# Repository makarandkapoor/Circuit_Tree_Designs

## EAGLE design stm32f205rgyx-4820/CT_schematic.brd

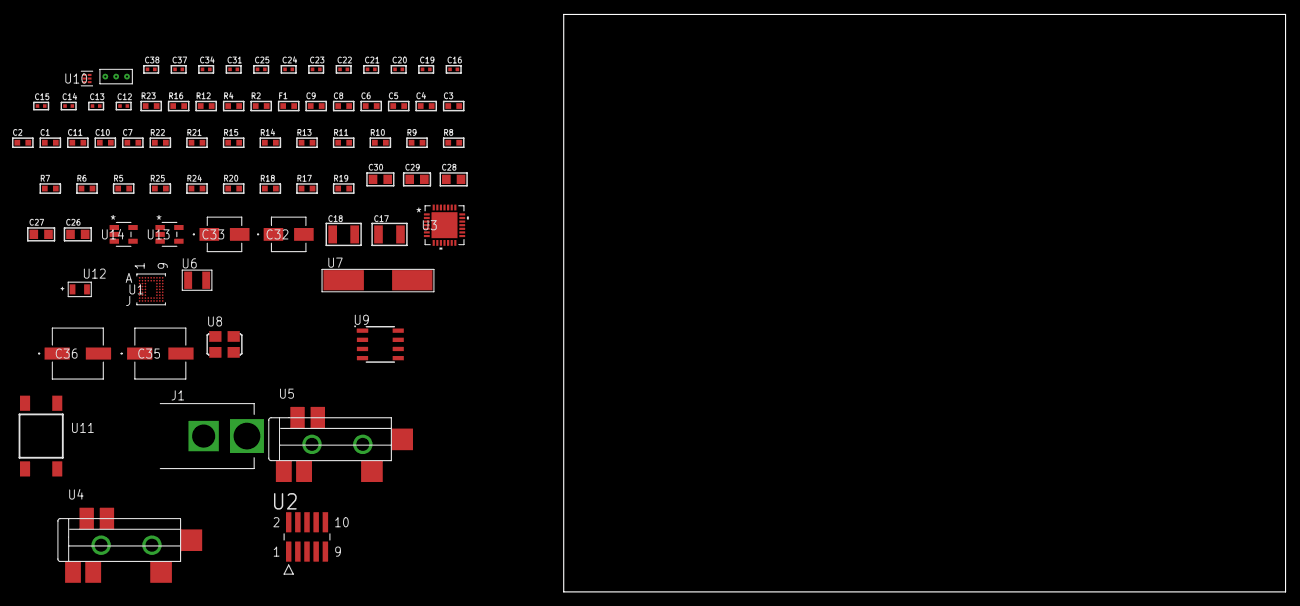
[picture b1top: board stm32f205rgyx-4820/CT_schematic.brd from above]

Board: 2 copper layers, 100.0 x 80.0 mm, 78 parts (0 on the bottom side), 38 nets, no tracks yet.

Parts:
C1, C9: 1e-06; C0603
C2, C3, C4, C5, C6: 1e-07; C0603
C7: 4.7e-06; C0603
C8: 1e-08; C0603
C10, C11: 2.2e-06; C0603
C12, C13, C14, C15: 1e-11; C0402
C16, C21, C22, C23, C24, C25, C34: 1e-07; C0402
C17, C18: 2.2e-05; C1210
C19, C20: 1e-09; C0402
C26, C27, C28, C29, C30: 1e-05; C0805
C31, C37, C38: 1e-08; C0402
C32: 1e-06; EXV-9B
C33: 2.2e-06; EXV-9B
C35, C36: 0.0001; EXV-9H
F1: 240.0; L0603
J1: PJ-037B; PJ-037B_PACKAGE
R2: 1000.0; R0603
R4: 4700.0; R0603
R5, R6, R7, R8, R9, R10, R11, R21, R22: 10000.0; R0603
R12: 5.0; R0603
R13, R14, R15: 47000.0; R0603
R16: 680.0; R0603
R17, R18, R20: 100000.0; R0603
R19: 164658.62; R0603
R23: 9100.0; R0603
R24: 680000.0; R0603
R25: 120000.0; R0603
U1: STM32F205RGY6; WLCSP66
U2: FTSH-105-01-L-DV-K; SAMTEC_FTSH-105-01-L-DV-K
U3: WM8731CLSEFL; QFN-28
U4, U5: SJ-43515TS-SMT-TR
U6: ABS07-32.768KHZ-7-T
U7: ABLS-25.000MHZ-B2F-T
U8: ASFL1-12.288MHZ-EC-T; ASFL1
U9: LP2954AIMX/NOPB; LP2954
U10: TPS3895ADRYR; SON-6
U11: 4-1437565-2; SW_4-1437565-2
U12: Q65110A2395; LGM67K-G1J2-24-Z
U13, U14: nc7sz125m5x; NC7SZ125M5X
U15: Dummy; DUMMY_PACKAGE_157

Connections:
CLK_CRYSTAL_U1_B9: C12.1, U1.B9, U6.1
CLK_CRYSTAL_U1_C9: C13.1, U1.C9, U6.2
CLK_CRYSTAL_U1_E9: C14.1, U1.E9, U7.1
CLK_CRYSTAL_U1_F9: C15.1, U1.F9, U7.2
CLK_U3_1: U3.1, U8.3
GND: C1.2, C2.2, C3.2, C4.2, C5.2, C6.2, C7.2, C8.2, C9.2, C10.2, C11.2, C12.2, C13.2, C14.2, C15.2, C16.2, C20.2, C21.2, C22.2, C23.2, C24.2, C25.2, C26.2, C27.2, C28.2, C29.2, C30.2, C31.2, C32.2, C33.2, C34.2, C35.2, C36.2, C37.2, C38.2, J1.2, R2.2, R5.2, R6.2, R7.2, R11.2, R12.2, R13.2, R14.2, R15.2, R20.2, R23.2, R25.2, U1.B1, U1.D8, U1.F1, U1.H9, U2.3, U2.5, U3.4, U3.15, U3.19, U3.25, U3.26, U3.29, U4.1, U5.1, U8.2, U9.4, U10.2, U12.C, U13.2, U13.3, U14.1, U14.3, U15.1
NET_U1_B6: R5.1, U1.B6
NET_U1_C2: C11.1, U1.C2
NET_U1_C8: R7.1, U1.C8
NET_U1_E8: R4.1, U1.E8, U14.4
NET_U1_F7: C8.1, C9.1, F1.1, U1.F7
NET_U1_H7: R6.1, U1.H7
NET_U1_J3: C10.1, U1.J3
NET_U1_J9: U11.3, U11.4
NET_U2_9: R12.1, U2.9
NET_U3_20: C25.1, C30.1, U3.20
NET_U4_2: C18.1, R14.1, U4.2
NET_U4_5: C17.1, R13.1, U4.5
NET_U5_5: C19.1, C20.1, R15.1, R16.1, U5.5
NET_U9_3: R18.1, U9.3
NET_U9_5: R17.1, U9.5
NET_U9_7: R19.2, R20.1, U9.7
NET_U10_1: R22.1, R23.1, U10.1
NET_U10_3: R24.2, R25.1, U10.3
NET_U10_4: R21.1, U10.4, U13.4, U14.2
NET_U11_1: R2.1, U11.1, U11.2
PROC_ADC1_IN1: U1.H8, U15.2
PROC_ADC1_IN3: U1.G7, U15.3
PROC_I2S2_SCK: U1.H2, U3.7
PROC_I2S2_SD: U1.G1, U3.8
PROC_I2S2_WS: U1.A7, U3.9, U3.11
PROC_SYS_JTCK_SWCLK: R11.1, U1.A1, U2.4
PROC_SYS_JTDI: R9.1, U1.A2, U2.8
PROC_SYS_JTDO_SWO: U1.A4, U2.6
PROC_SYS_JTMS_SWDIO: R10.1, U1.B2, U2.2
RST_OUT_U2_JTAG_RST_B: R8.1, U2.10, U13.1
VCC_S1_7V0: C32.1, C35.1, C36.1, J1.1, R18.2, U9.8
VCC_TIER1_3V3: C1.1, C2.1, C3.1, C4.1, C5.1, C6.1, C7.1, C16.1, C21.1, C22.1, C23.1, C24.1, C26.1, C27.1, C28.1, C29.1, C31.1, C33.1, C34.1, C37.1, C38.1, F1.2, R4.2, R8.2, R9.2, R10.2, R17.2, R19.1, R21.2, R22.2, R24.1, U1.A8, U1.A9, U1.D9, U1.E1, U2.1, U3.3, U3.5, U3.12, U3.18, U8.4, U9.1, U10.6, U13.5, U14.5

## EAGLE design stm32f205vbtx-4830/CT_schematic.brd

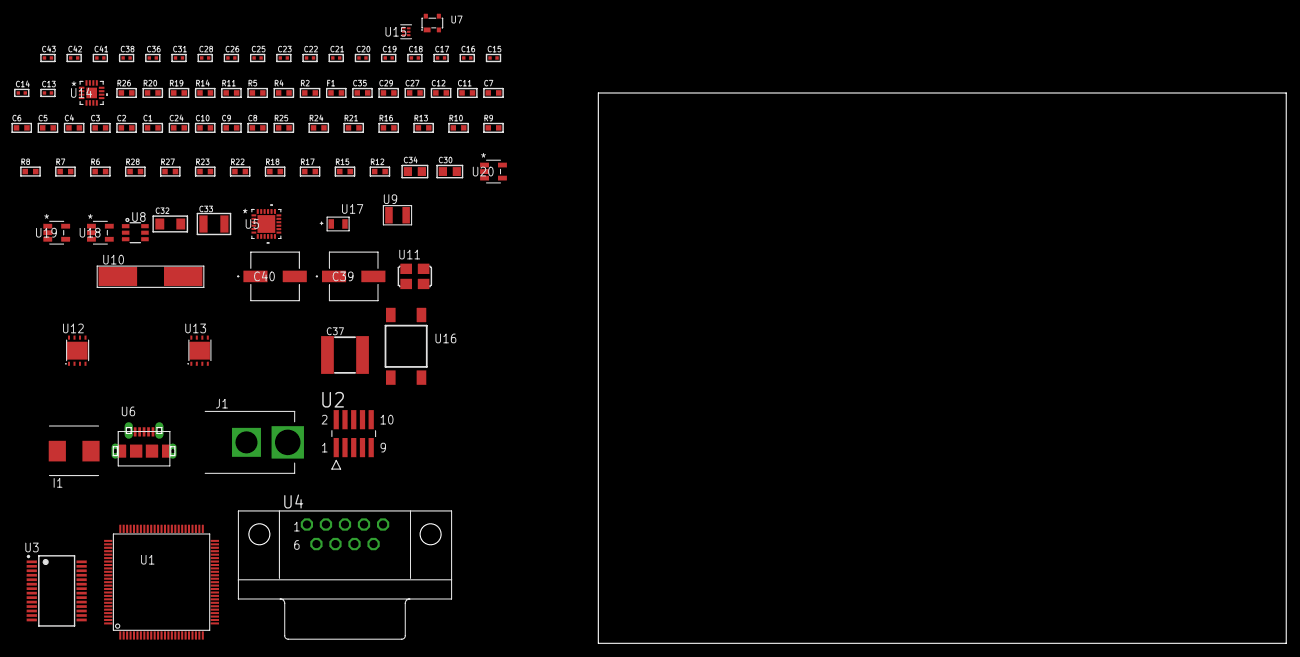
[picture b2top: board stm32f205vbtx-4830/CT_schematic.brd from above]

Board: 2 copper layers, 92 parts (0 on the bottom side), 71 nets, no tracks yet.

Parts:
C1, C12, C27, C29, C35: 1e-06; C0603
C2, C3, C4, C5, C6, C7: 1e-07; C0603
C8: 4.7e-06; C0603
C9, C10, C24: 2.2e-06; C0603
C11: 1e-08; C0603
C13, C14, C15, C16: 1e-11; C0402
C17, C18, C19, C20, C21, C22, C36, C38: 1e-07; C0402
C23, C25, C26, C28, C31, C41, C42, C43: 1e-08; C0402
C30, C34: 1e-05; C0805
C32: 1e-05; C1206
C33: 1e-05; C1210
C37: 6.8e-05; 2220
C39, C40: 0.0001; EXV-9H
F1: 240.0; L0603
I1: 3.3e-06; WE-HCI_7030/7040/7050
J1: PJ-037B; PJ-037B_PACKAGE
R2, R20: 1000.0; R0603
R4, R5: 4700.0; R0603
R6, R7, R8, R9, R10, R24, R25: 10000.0; R0603
R11: 5.0; R0603
R12, R15, R17, R18: 100000.0; R0603
R13: 47000.0; R0603
R14: 8060.0; R0603
R16: 36000.0; R0603
R19: 2231.0; R0603
R21: 20000.0; R0603
R22: 150000.0; R0603
R23: 300000.0; R0603
R26: 9100.0; R0603
R27: 680000.0; R0603
R28: 120000.0; R0603
U1: STM32F205VBT6; LQFP100
U2: FTSH-105-01-L-DV-K; SAMTEC_FTSH-105-01-L-DV-K
U3: ST3241EBPR; SSOP-28
U4: 182-009-113R531; 182-009-MALE
U5: USB3317C-CP-TR; QFN-24
U6: 47590-0001; MICRO_USB_AB
U7: prtr5v0u2ax; SOT143B
U8: MAX4995AAUT+T; SOT-23-6
U9: ABS07-32.768KHZ-7-T
U10: ABLS-25.000MHZ-B2F-T
U11: ASFL1-26MHZ-NCS; ASFL1
U12: LP2951ACSDX/NOPB; WSON-8
U13: LP3878SDX-ADJ/NOPB; WSON-8
U14: LTC3601EUD#PBF; QFN-16_EP
U15: TPS3895ADRYR; SON-6
U16: 4-1437565-2; SW_4-1437565-2
U17: Q65110A2395; LGM67K-G1J2-24-Z
U18, U19, U20: nc7sz125m5x; NC7SZ125M5X

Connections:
CLK_CRYSTAL_U1_8: C13.1, U1.8, U9.1
CLK_CRYSTAL_U1_9: C14.1, U1.9, U9.2
CLK_CRYSTAL_U1_12: C15.1, U1.12, U10.1
CLK_CRYSTAL_U1_13: C16.1, U1.13, U10.2
CLK_U5_23: U5.23, U11.3
GND: C1.2, C2.2, C3.2, C4.2, C5.2, C6.2, C7.2, C8.2, C9.2, C10.2, C11.2, C12.2, C13.2, C14.2, C15.2, C16.2, C17.2, C18.2, C21.2, C22.2, C23.2, C24.2, C25.2, C26.2, C27.2, C28.2, C29.2, C30.2, C31.2, C32.2, C33.2, C34.2, C35.2, C37.1, C37.2, C38.2, C39.2, C40.2, C41.2, C42.2, C43.2, J1.2, R2.2, R6.2, R10.2, R11.2, R13.2, R14.2, R17.2, R20.2, R21.2, R23.2, R26.2, R28.2, U1.10, U1.20, U1.27, U1.74, U2.3, U2.5, U3.23, U3.25, U4.5, U5.25, U6.5, U6.6, U6.7, U6.8, U6.9, U7.1, U8.2, U11.2, U12.3, U12.4, U12.PAD, U13.3, U13.PAD, U14.1, U14.9, U14.17, U15.2, U17.C, U18.2, U18.3, U19.1, U19.3, U20.1, U20.3
NET_U1_14: R4.1, U1.14, U19.4
NET_U1_22: C11.1, C12.1, F1.1, U1.21, U1.22
NET_U1_49: C9.1, U1.49
NET_U1_73: C10.1, U1.73
NET_U1_94: R6.1, U1.94
NET_U1_98: U16.3, U16.4
NET_U2_9: R11.1, U2.9
NET_U3_1: C20.1, U3.1
NET_U3_2: C20.2, U3.2
NET_U3_3: C22.1, U3.3
NET_U3_22: R12.1, U3.22
NET_U3_24: C19.2, U3.24
NET_U3_27: C21.1, U3.27
NET_U3_28: C19.1, U3.28
NET_U4_2: U3.4, U4.2
NET_U4_3: U3.9, U4.3
NET_U4_7: U3.5, U4.7
NET_U4_8: U3.10, U4.8
NET_U5_4: C24.1, U5.4
NET_U5_22: R5.1, U5.22, U20.4
NET_U5_24: R14.1, U5.24
NET_U6_1: C27.1, U5.2, U6.1, U7.4, U8.1
NET_U6_2: U5.5, U6.2, U7.3
NET_U6_3: U5.6, U6.3, U7.2
NET_U6_4: U5.1, U6.4
NET_U8_3: R13.1, U8.3
NET_U8_4: U5.7, U8.4
NET_U12_5: R15.1, U12.5
NET_U12_7: R16.2, R17.1, U12.7
NET_U13_1: C31.1, U13.1
NET_U13_6: R19.2, R20.1, U13.6
NET_U13_8: R18.1, U13.8
NET_U14_3: C36.2, I1.1, U14.3, U14.4
NET_U14_6: C36.1, U14.6
NET_U14_7: C35.1, U14.7, U14.12
NET_U14_10: R23.1, U14.10
NET_U14_11: R21.1, R22.1, U14.11
NET_U14_ATNET_3: I1.2, R22.2
NET_U15_1: R25.1, R26.1, U15.1
NET_U15_3: R27.2, R28.1, U15.3
NET_U15_4: R24.1, U15.4, U18.4, U19.2, U20.2
NET_U16_1: R2.1, U16.1, U16.2
PROC_SYS_JTCK_SWCLK: R10.1, U1.76, U2.4
PROC_SYS_JTDI: R8.1, U1.77, U2.8
PROC_SYS_JTDO_SWO: U1.89, U2.6
PROC_SYS_JTMS_SWDIO: R9.1, U1.72, U2.2
PROC_UART4_RX: U1.24, U3.19
PROC_UART4_TX: U1.23, U3.14
PROC_USB_OTG_HS_ULPI_CK: U1.30, U5.12
PROC_USB_OTG_HS_ULPI_D0: U1.26, U5.16
PROC_USB_OTG_HS_ULPI_D1: U1.35, U5.15
PROC_USB_OTG_HS_ULPI_D2: U1.36, U5.14
PROC_USB_OTG_HS_ULPI_D3: U1.47, U5.13
PROC_USB_OTG_HS_ULPI_D4: U1.48, U5.11
PROC_USB_OTG_HS_ULPI_D5: U1.51, U5.10
PROC_USB_OTG_HS_ULPI_D6: U1.52, U5.9
PROC_USB_OTG_HS_ULPI_D7: U1.91, U5.8
PROC_USB_OTG_HS_ULPI_DIR: U1.17, U5.19
PROC_USB_OTG_HS_ULPI_NXT: U1.18, U5.18
PROC_USB_OTG_HS_ULPI_STP: U1.15, U5.20
RST_OUT_U2_JTAG_RST_B: R7.1, U2.10, U18.1
VCC_S1_5V9: C29.1, C32.1, C34.1, C39.1, C40.1, J1.1, R18.2, U12.8, U13.4, U14.15, U14.16
VCC_TIER1_1V8: C26.1, C30.1, C41.1, C42.1, C43.1, R15.2, R16.1, U5.21, U12.1, U18.5, U19.5, U20.5
VCC_TIER1_3V3: C1.1, C2.1, C3.1, C4.1, C5.1, C6.1, C7.1, C8.1, C17.1, C18.1, C23.1, C25.1, C28.1, C33.1, C38.1, F1.2, R4.2, R5.2, R7.2, R8.2, R9.2, R12.2, R19.1, R24.2, R25.2, R27.1, U1.6, U1.11, U1.19, U1.28, U1.50, U1.75, U1.100, U2.1, U3.26, U5.3, U5.17, U11.4, U13.5, U15.6
VCC_TIER1_5V0: C37.2, I1.2, R22.2, U8.5, U14.8

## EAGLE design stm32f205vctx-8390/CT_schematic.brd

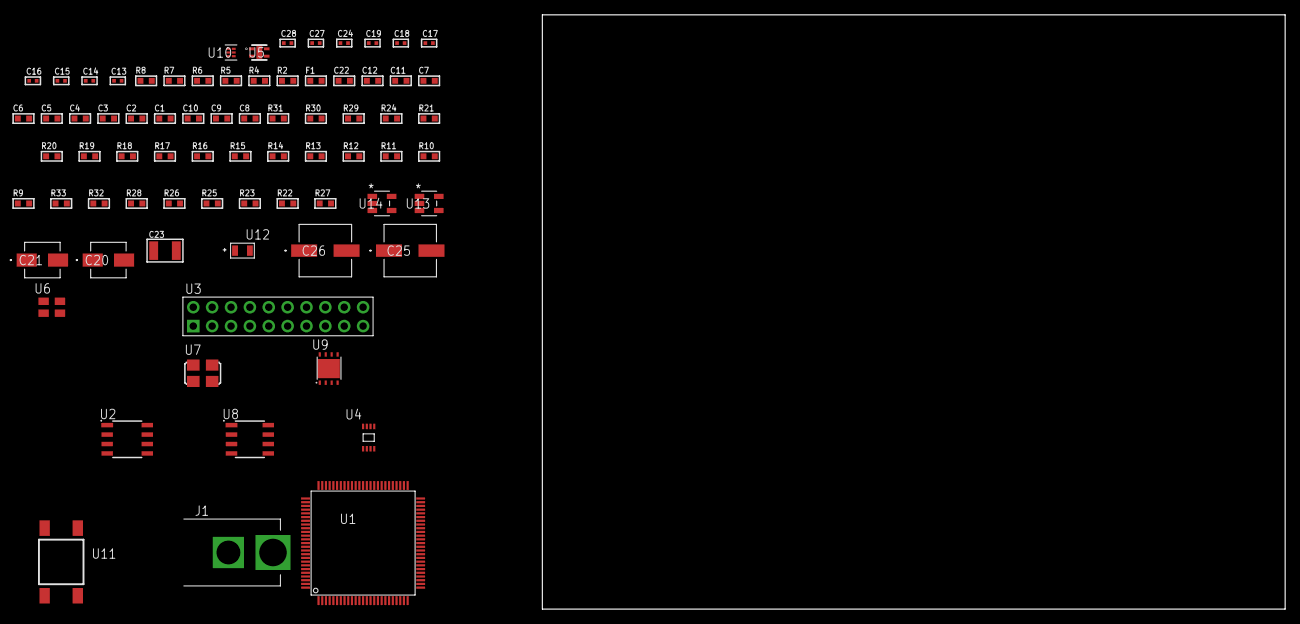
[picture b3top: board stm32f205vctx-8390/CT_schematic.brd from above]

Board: 2 copper layers, 100.0 x 80.0 mm, 75 parts (0 on the bottom side), 41 nets, no tracks yet.

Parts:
C1, C12: 1e-06; C0603
C2, C3, C4, C5, C6, C7: 1e-07; C0603
C8: 4.7e-06; C0603
C9, C10: 2.2e-06; C0603
C11: 1e-08; C0603
C13, C16, C18, C19, C27, C28: 1e-08; C0402
C14, C15, C17, C24: 1e-07; C0402
C20: 1e-06; EXV-9B
C21: 2.2e-06; EXV-9B
C22: 8e-07; R0603
C23: 1e-05; C1210
C25, C26: 0.0001; EXV-9H
F1: 240.0; L0603
J1: PJ-037B; PJ-037B_PACKAGE
R2: 1000.0; R0603
R4: 4700.0; R0603
R5, R6, R7, R8: 2200.0; R0603
R9, R10, R11, R12, R13, R14, R15, R16, R17, R18, R19, R20, R21, R29, R30: 10000.0; R0603
R22, R23, R25, R26, R28: 100000.0; R0603
R24: 47000.0; R0603
R27: 153694.38; R0603
R31: 82000.0; R0603
R32: 300000.0; R0603
R33: 120000.0; R0603
U1: STM32F205VCT6; LQFP100
U2: AT25040B-SSHL-T; SOIC-8
U3: TST-110-05-T-D-RA
U4: 24AA64T-I/MNY; TDFN-8/6MM
U5: Si7034-A10-IM; SI7034-A10-IM
U6: ASEK-32.768KHz-ECST; ASEK
U7: ASFL1-25MHZ-NCS; ASFL1
U8: LP2954AIMX/NOPB; LP2954
U9: LP2951ACSDX/NOPB; WSON-8
U10: TPS3895ADRYR; SON-6
U11: 4-1437565-2; SW_4-1437565-2
U12: Q65110A2395; LGM67K-G1J2-24-Z
U13, U14: nc7sz125m5x; NC7SZ125M5X

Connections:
CLK_U1_8: U1.8, U6.3
CLK_U1_12: U1.12, U7.3
GND: C1.2, C2.2, C3.2, C4.2, C5.2, C6.2, C7.2, C8.2, C9.2, C10.2, C11.2, C12.2, C13.2, C14.2, C15.2, C16.2, C17.2, C18.2, C19.2, C20.2, C21.2, C22.2, C23.2, C24.2, C25.2, C26.2, C27.2, C28.2, J1.2, R2.2, R9.2, R18.2, R20.2, R25.2, R28.2, R31.2, R33.2, U1.10, U1.27, U1.74, U2.4, U3.4, U3.6, U3.8, U3.10, U3.12, U3.14, U3.16, U3.18, U3.20, U4.4, U4.7, U5.5, U6.2, U7.2, U8.4, U9.3, U9.4, U9.PAD, U10.2, U12.C, U13.2, U13.3, U14.1, U14.3
NET_U1_14: R4.1, U1.14, U14.4
NET_U1_22: C11.1, C12.1, F1.1, U1.22
NET_U1_47: R7.1, U1.47, U4.6
NET_U1_48: R8.1, U1.48, U4.5
NET_U1_49: C9.1, U1.49
NET_U1_73: C10.1, U1.73
NET_U1_92: R5.1, U1.92, U5.2
NET_U1_93: R6.1, U1.93, U5.4
NET_U1_94: R9.1, U1.94
NET_U1_98: U11.3, U11.4
NET_U2_3: R10.1, U2.3
NET_U2_7: R12.1, U2.7
NET_U3_19: R18.1, U3.19
NET_U4_1: R19.1, U4.1
NET_U4_2: R20.1, U4.2
NET_U4_3: R21.1, U4.3
NET_U8_3: R23.1, U8.3
NET_U8_5: R22.1, U8.5
NET_U8_7: R24.2, R25.1, U8.7
NET_U9_5: R26.1, U9.5
NET_U9_7: R27.2, R28.1, U9.7
NET_U10_1: R30.1, R31.1, U10.1
NET_U10_3: R32.2, R33.1, U10.3
NET_U10_4: R29.1, U10.4, U13.4, U14.2
NET_U11_1: R2.1, U11.1, U11.2
PROC_SPI1_MISO: U1.31, U2.2
PROC_SPI1_MOSI: U1.32, U2.5
PROC_SPI1_NSS: R11.1, U1.29, U2.1
PROC_SPI1_SCK: U1.30, U2.6
PROC_SYS_JTCK_SWCLK: R16.1, U1.76, U3.9
PROC_SYS_JTDI: R14.1, U1.77, U3.5
PROC_SYS_JTDO_SWO: U1.89, U3.13
PROC_SYS_JTMS_SWDIO: R15.1, U1.72, U3.7
PROC_SYS_JTRST: R13.1, U1.90, U3.3
RST_OUT_U3_SRESET_B: R17.1, U3.15, U13.1
VCC_S1_14V8: C20.1, C22.1, C25.1, C26.1, J1.1, R23.2, U8.8, U9.8
VCC_TIER1_1V8: C1.1, C2.1, C3.1, C4.1, C5.1, C6.1, C7.1, C8.1, C13.1, C15.1, C16.1, C17.1, C21.1, C24.1, C27.1, C28.1, F1.2, R4.2, R5.2, R6.2, R7.2, R8.2, R10.2, R11.2, R12.2, R13.2, R14.2, R15.2, R16.2, R17.2, R19.2, R21.2, R22.2, R24.1, R29.2, R30.2, R32.1, U1.6, U1.11, U1.19, U1.28, U1.50, U1.75, U1.100, U2.8, U3.1, U4.8, U5.1, U8.1, U10.6, U13.5, U14.5
VCC_TIER1_3V3: C14.1, C18.1, C19.1, C23.1, R26.2, R27.1, U3.2, U6.4, U7.4, U9.1

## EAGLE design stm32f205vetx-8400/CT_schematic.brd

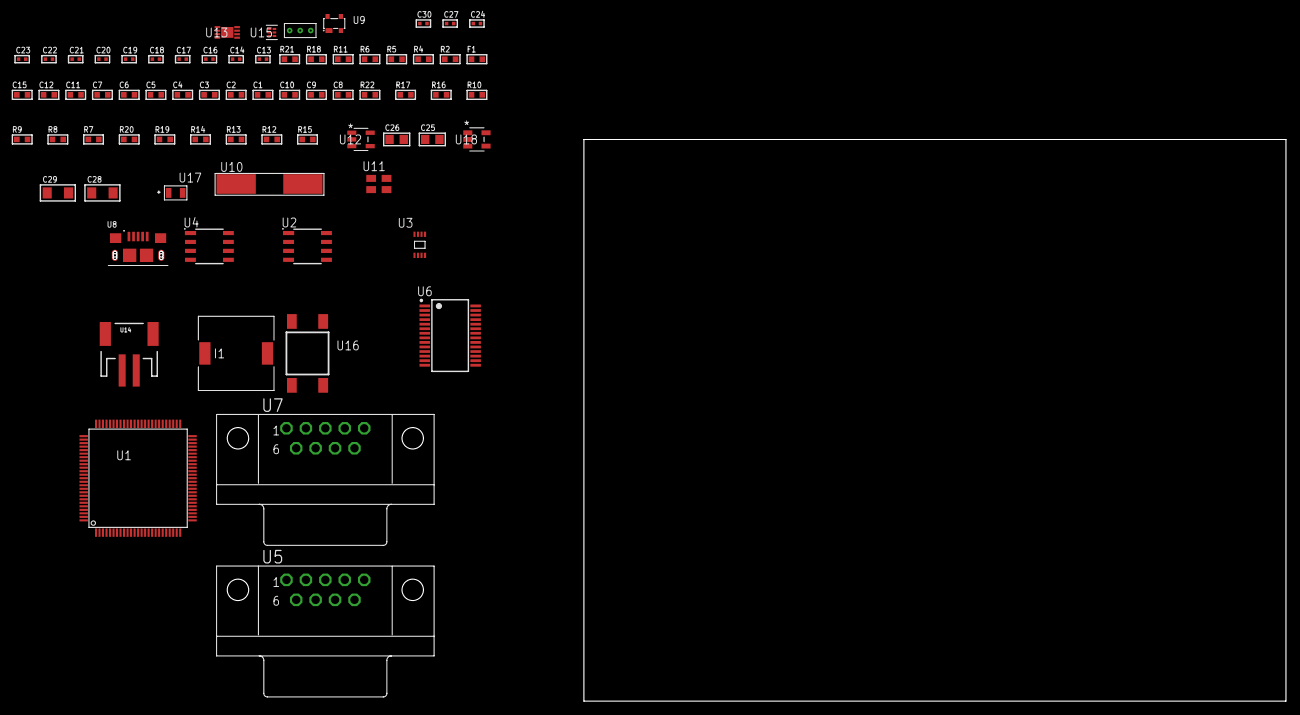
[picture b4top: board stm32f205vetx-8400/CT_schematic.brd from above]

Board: 2 copper layers, 71 parts (0 on the bottom side), 53 nets, no tracks yet.

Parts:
C1, C12, C15: 1e-06; C0603
C2, C3, C4, C5, C6, C7: 1e-07; C0603
C8: 4.7e-06; C0603
C9, C10: 2.2e-06; C0603
C11: 1e-08; C0603
C13, C14: 1e-11; C0402
C16, C17, C24, C30: 1e-08; C0402
C18, C19, C20, C21, C22, C23, C27: 1e-07; C0402
C25, C26: 1e-05; C0805
C28, C29: 1e-05; C1206
F1: 240.0; L0603
I1: 2.5e-06; DR1040
R2: 1000.0; R0603
R4: 4700.0; R0603
R5, R6: 2200.0; R0603
R7, R8, R9, R10, R16, R17, R22: 10000.0; R0603
R11: 120.0; R0603
R12: 470000.0; R0603
R13: 100000.0; R0603
R14: 220000.0; R0603
R15: 1000000.0; R0603
R18: 9100.0; R0603
R19: 680000.0; R0603
R20: 120000.0; R0603
R21: 2000.0; R0603
U1: STM32F205VET7; LQFP100
U2: AT25040B-SSHL-T; SOIC-8
U3: 24AA00T-I/MNY; TDFN-8/6MM
U4: SN65HVD230D; SOIC-8
U5, U7: 182-009-113R531; 182-009-MALE
U6: ST3241EBPR; SSOP-28
U8: 10118193-0001LF; FCI_10118193-0001LF
U9: prtr5v0u2ax; SOT143B
U10: ABLS-25.000MHZ-B2F-T
U11: ASEK-32.768KHz-ECST; ASEK
U12: ltc3406es5; TSOT-23-5
U13: MCP73831T-2ACI/MC; DFN8_2X3MC
U14: S2B-PH-SM4-TB(LF)(SN); JST-2-SMD
U15: TPS3895ADRYR; SON-6
U16: 4-1437565-2; SW_4-1437565-2
U17: Q65110A2395; LGM67K-G1J2-24-Z
U18: nc7sz125m5x; NC7SZ125M5X
U19: Dummy; DUMMY_PACKAGE_156

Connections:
CLK_CRYSTAL_U1_12: C13.1, U1.12, U10.1
CLK_CRYSTAL_U1_13: C14.1, U1.13, U10.2
CLK_U1_8: U1.8, U11.3
GND: C1.2, C2.2, C3.2, C4.2, C5.2, C6.2, C7.2, C8.2, C9.2, C10.2, C11.2, C12.2, C13.2, C14.2, C15.2, C16.2, C17.2, C18.2, C19.2, C22.2, C23.2, C24.2, C25.2, C26.1, C26.2, C27.2, C28.2, C29.2, C30.2, R2.2, R7.2, R12.2, R14.2, R18.2, R20.2, R21.2, U1.10, U1.20, U1.27, U1.70, U1.74, U2.4, U3.4, U4.2, U5.5, U6.23, U6.25, U7.5, U8.5, U8.6, U8.7, U8.8, U8.9, U9.1, U11.2, U12.2, U13.6, U13.9, U14.2, U15.2, U17.C, U18.1, U18.3, U19.1
INPUT_USBPOWER_5V: C15.1, C28.1, R22.2, U1.68, U8.1, U9.4, U13.1, U13.2
NET_U1_14: R4.1, U1.14, U18.4
NET_U1_22: C11.1, C12.1, F1.1, U1.21, U1.22
NET_U1_49: C9.1, U1.49
NET_U1_73: C10.1, U1.73
NET_U1_92: R5.1, U1.92, U3.6
NET_U1_93: R6.1, U1.93, U3.5
NET_U1_94: R7.1, U1.94
NET_U1_98: U16.3, U16.4
NET_U2_3: R8.1, U2.3
NET_U2_7: R10.1, U2.7
NET_U4_6: R11.2, U4.6
NET_U4_8: R12.1, U4.8
NET_U5_2: R11.2, U4.6, U5.2
NET_U5_3: R11.1, U4.7, U5.3
NET_U6_1: C21.1, U6.1
NET_U6_2: C21.2, U6.2
NET_U6_3: C23.1, U6.3
NET_U6_22: R13.1, U6.22
NET_U6_24: C20.2, U6.24
NET_U6_27: C22.1, U6.27
NET_U6_28: C20.1, U6.28
NET_U7_2: U6.4, U7.2
NET_U7_3: U6.9, U7.3
NET_U7_7: U6.5, U7.7
NET_U7_8: U6.10, U7.8
NET_U12_3: I1.1, U12.3
NET_U12_5: R14.1, R15.1, U12.5
NET_U12_ATNET_3: I1.2, R15.2
NET_U13_5: R22.1, U13.5
NET_U13_8: R21.1, U13.8
NET_U15_1: R17.1, R18.1, U15.1
NET_U15_3: R19.2, R20.1, U15.3
NET_U15_4: R16.1, U15.4, U18.2
NET_U16_1: R2.1, U16.1, U16.2
PROC_CAN1_RX: U1.81, U4.4
PROC_CAN1_TX: U1.82, U4.1
PROC_SPI1_MISO: U1.31, U2.2
PROC_SPI1_MOSI: U1.32, U2.5
PROC_SPI1_NSS: R9.1, U1.29, U2.1
PROC_SPI1_SCK: U1.30, U2.6
PROC_TIM1_CH2: U1.42, U19.2
PROC_TIM1_CH4: U1.45, U19.3
PROC_UART4_RX: U1.24, U6.19
PROC_UART4_TX: U1.23, U6.14
PROC_USB_OTG_FS_DM: U1.70, U8.2, U9.3
PROC_USB_OTG_FS_DP: U1.71, U8.3, U9.2
VCC_S1_3V7: C25.1, C29.1, U12.4, U13.3, U13.4, U14.1
VCC_TIER1_3V3: C1.1, C2.1, C3.1, C4.1, C5.1, C6.1, C7.1, C8.1, C16.1, C17.1, C18.1, C19.1, C24.1, C26.2, C27.1, C30.1, F1.2, I1.2, R4.2, R5.2, R6.2, R8.2, R9.2, R10.2, R13.2, R15.2, R16.2, R17.2, R19.1, U1.6, U1.11, U1.19, U1.28, U1.50, U1.75, U1.100, U2.8, U3.8, U4.3, U6.26, U11.4, U15.6, U18.5

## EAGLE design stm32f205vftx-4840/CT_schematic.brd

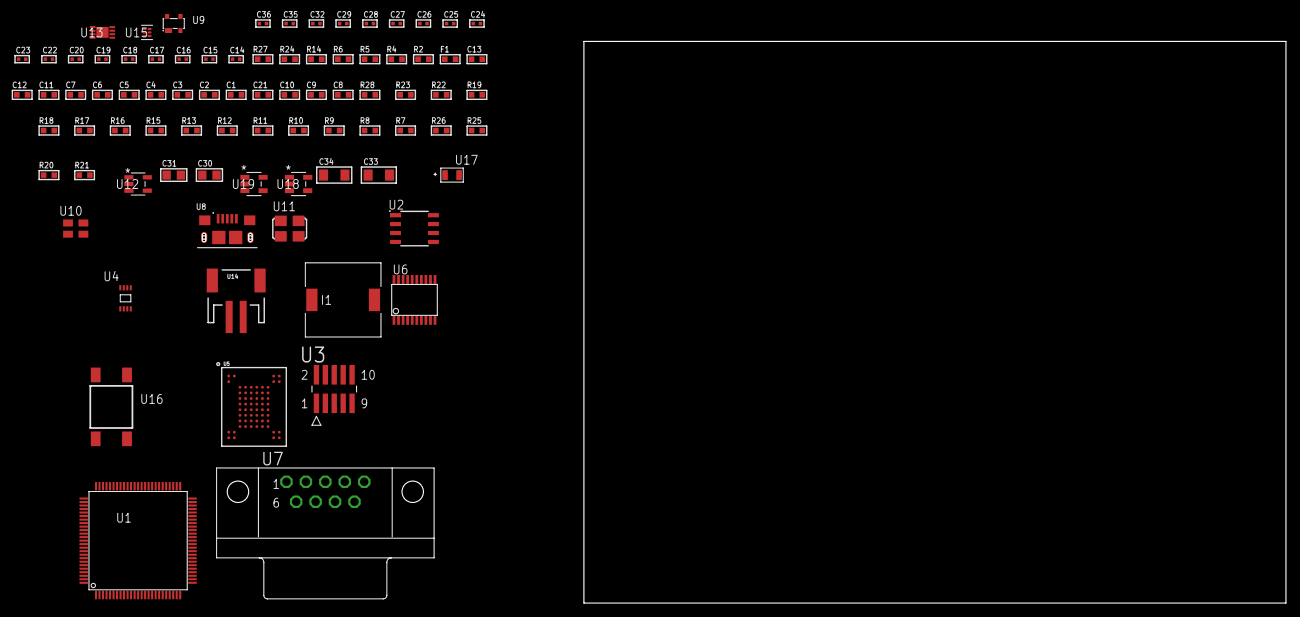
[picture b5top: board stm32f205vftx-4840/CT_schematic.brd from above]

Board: 2 copper layers, 83 parts (0 on the bottom side), 61 nets, no tracks yet.

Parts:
C1, C12, C13: 1e-06; C0603
C2, C3, C4, C5, C6, C7: 1e-07; C0603
C8: 4.7e-06; C0603
C9, C10, C21: 2.2e-06; C0603
C11: 1e-08; C0603
C14, C16, C28, C29, C35, C36: 1e-08; C0402
C15, C17, C18, C19, C20, C22, C23, C24, C25, C26, C27, C32: 1e-07; C0402
C30, C31: 1e-05; C0805
C33, C34: 1e-05; C1206
F1: 240.0; L0603
I1: 3.8e-06; DR1040
R2: 1000.0; R0603
R4: 4700.0; R0603
R5, R6: 2200.0; R0603
R7, R8, R9, R10, R11, R12, R13, R15, R16, R17, R18, R19, R22, R23, R28: 10000.0; R0603
R14: 5.0; R0603
R20: 220000.0; R0603
R21: 1000000.0; R0603
R24: 9100.0; R0603
R25: 680000.0; R0603
R26: 120000.0; R0603
R27: 2000.0; R0603
U1: STM32F205VFT6; LQFP100
U2: AT25320B-SSHL-T; SOIC-8
U3: FTSH-105-01-L-DV-K; SAMTEC_FTSH-105-01-L-DV-K
U4: 24AA00T-I/MNY; TDFN-8/6MM
U5: mt29f4g08abadah4; VFBGA-63
U6: SP3203ECY-L/TR; TSSOP20-I
U7: 182-009-113R531; 182-009-MALE
U8: 10118193-0001LF; FCI_10118193-0001LF
U9: prtr5v0u2ax; SOT143B
U10: ASEK-32.768KHz-ECST; ASEK
U11: ASFL1-25MHZ-NCS; ASFL1
U12: ltc3406es5; TSOT-23-5
U13: MCP73831T-2ACI/MC; DFN8_2X3MC
U14: S2B-PH-SM4-TB(LF)(SN); JST-2-SMD
U15: TPS3895ADRYR; SON-6
U16: 4-1437565-2; SW_4-1437565-2
U17: Q65110A2395; LGM67K-G1J2-24-Z
U18, U19: nc7sz125m5x; NC7SZ125M5X

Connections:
CLK_U1_8: U1.8, U10.3
CLK_U1_12: U1.12, U11.3
GND: C1.2, C2.2, C3.2, C4.2, C5.2, C6.2, C7.2, C8.2, C9.2, C10.2, C11.2, C12.2, C13.2, C14.2, C15.2, C16.2, C17.2, C18.2, C19.2, C20.2, C21.2, C22.2, C23.2, C26.2, C27.2, C28.2, C29.2, C30.2, C31.1, C31.2, C32.2, C33.2, C34.2, C35.2, C36.2, R2.2, R7.2, R14.2, R20.2, R24.2, R26.2, R27.2, U1.10, U1.20, U1.27, U1.70, U1.74, U2.4, U3.3, U3.5, U4.4, U5.C5, U5.F7, U5.K3, U5.K8, U6.18, U7.5, U8.5, U8.6, U8.7, U8.8, U8.9, U9.1, U10.2, U11.2, U12.2, U13.6, U13.9, U14.2, U15.2, U17.C, U18.2, U18.3, U19.1, U19.3
INPUT_USBPOWER_5V: C13.1, C33.1, R28.2, U1.68, U8.1, U9.4, U13.1, U13.2
NET_U1_14: R4.1, U1.14, U19.4
NET_U1_22: C11.1, C12.1, F1.1, U1.21, U1.22
NET_U1_49: C9.1, U1.49
NET_U1_73: C10.1, U1.73
NET_U1_92: R5.1, U1.92, U4.6
NET_U1_93: R6.1, U1.93, U4.5
NET_U1_94: R7.1, U1.94
NET_U1_98: U16.3, U16.4
NET_U2_3: R8.1, U2.3
NET_U2_7: R10.1, U2.7
NET_U3_9: R14.1, U3.9
NET_U5_C3: R19.1, U5.C3
NET_U6_1: C24.1, U6.1
NET_U6_2: C26.1, U6.2
NET_U6_3: C24.2, U6.3
NET_U6_4: C25.1, U6.4
NET_U6_5: C25.2, U6.5
NET_U6_6: C27.1, U6.6
NET_U7_2: U6.14, U7.2
NET_U7_3: U6.17, U7.3
NET_U7_7: U6.13, U7.7
NET_U7_8: U6.16, U7.8
NET_U12_3: I1.1, U12.3
NET_U12_5: R20.1, R21.1, U12.5
NET_U12_ATNET_3: I1.2, R21.2
NET_U13_5: R28.1, U13.5
NET_U13_8: R27.1, U13.8
NET_U15_1: R23.1, R24.1, U15.1
NET_U15_3: R25.2, R26.1, U15.3
NET_U15_4: R22.1, U15.4, U18.4, U19.2
NET_U16_1: R2.1, U16.1, U16.2
PROC_FSMC_D0: U1.61, U5.H4
PROC_FSMC_D1: U1.62, U5.J4
PROC_FSMC_D2: U1.81, U5.K4
PROC_FSMC_D3: U1.82, U5.K5
PROC_FSMC_D4: U1.38, U5.K6
PROC_FSMC_D5: U1.39, U5.J7
PROC_FSMC_D6: U1.40, U5.K7
PROC_FSMC_D7: U1.41, U5.J8
PROC_FSMC_NCE2: R16.1, U1.88, U5.C6
PROC_FSMC_NOE: R18.1, U1.85, U5.D4
PROC_FSMC_NWAIT: R15.1, U1.87, U5.C8
PROC_FSMC_NWE: R17.1, U1.86, U5.C7
PROC_SPI1_MISO: U1.31, U2.2
PROC_SPI1_MOSI: U1.32, U2.5
PROC_SPI1_NSS: R9.1, U1.29, U2.1
PROC_SPI1_SCK: U1.30, U2.6
PROC_SYS_JTCK_SWCLK: R12.1, U1.76, U3.4
PROC_SYS_JTDO_SWO: U1.89, U3.6
PROC_SYS_JTMS_SWDIO: R13.1, U1.72, U3.2
PROC_UART4_RX: U1.24, U6.11
PROC_UART4_TX: U1.23, U6.7
PROC_USB_OTG_FS_DM: U1.70, U8.2, U9.3
PROC_USB_OTG_FS_DP: U1.71, U8.3, U9.2
RST_OUT_U3_JTAG_RST_B: R11.1, U3.10, U18.1
VCC_S1_3V7: C30.1, C34.1, U12.4, U13.3, U13.4, U14.1
VCC_TIER1_3V3: C1.1, C2.1, C3.1, C4.1, C5.1, C6.1, C7.1, C8.1, C14.1, C15.1, C16.1, C17.1, C18.1, C19.1, C20.1, C21.1, C22.1, C23.1, C28.1, C29.1, C31.2, C32.1, C35.1, C36.1, F1.2, I1.2, R4.2, R5.2, R6.2, R8.2, R9.2, R10.2, R11.2, R12.2, R13.2, R15.2, R16.2, R17.2, R18.2, R19.2, R21.2, R22.2, R23.2, R25.1, U1.6, U1.11, U1.19, U1.28, U1.50, U1.75, U1.100, U2.8, U3.1, U4.8, U5.D3, U5.G4, U5.H8, U5.J6, U6.12, U6.19, U10.4, U11.4, U15.6, U18.5, U19.5

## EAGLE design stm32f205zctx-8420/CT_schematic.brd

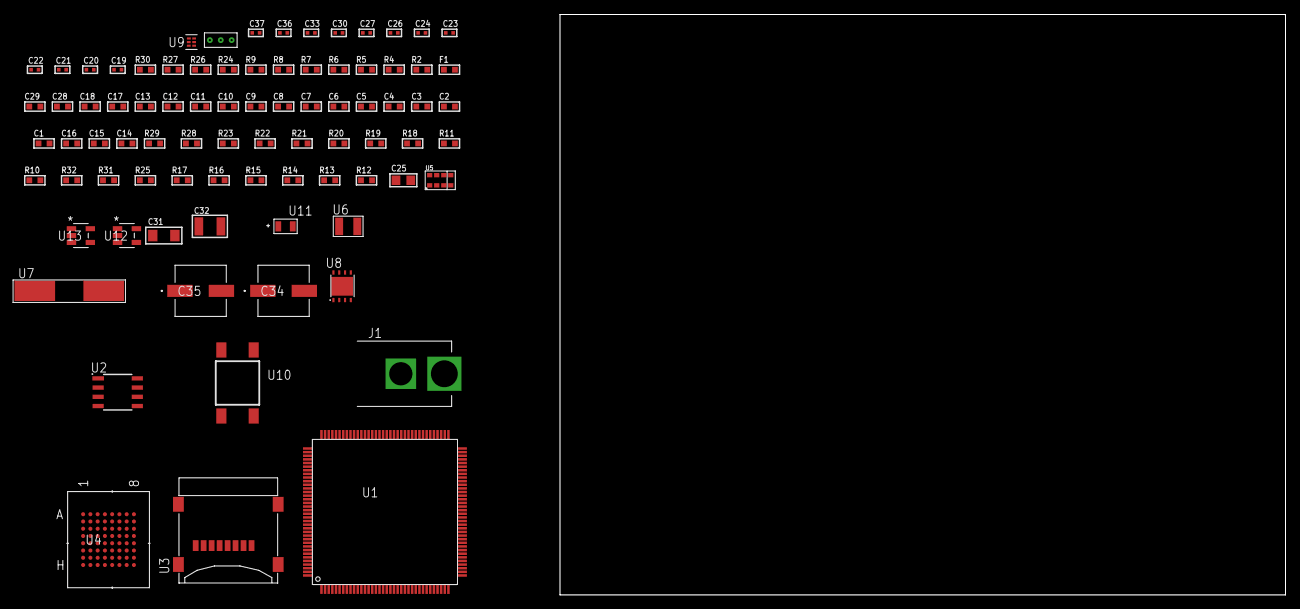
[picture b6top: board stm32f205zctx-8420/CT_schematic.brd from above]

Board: 2 copper layers, 100.0 x 80.0 mm, 83 parts (0 on the bottom side), 81 nets, no tracks yet.

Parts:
C1, C18, C28, C29: 1e-06; C0603
C2, C3, C4, C5, C6, C7, C8, C9, C10, C11, C12, C13: 1e-07; C0603
C14: 4.7e-06; C0603
C15, C16: 2.2e-06; C0603
C17: 1e-08; C0603
C19, C20, C21, C22: 1e-11; C0402
C23, C26, C27, C30, C36, C37: 1e-08; C0402
C24, C33: 1e-07; C0402
C25: 1e-05; C0805
C31: 1e-05; C1206
C32: 1e-05; C1210
C34, C35: 0.0001; EXV-9H
F1: 240.0; L0603
J1: PJ-037B; PJ-037B_PACKAGE
R2, R27: 1000.0; R0603
R4, R5: 4700.0; R0603
R6, R7, R8, R9: 2200.0; R0603
R10, R11, R18, R19, R20, R21, R22, R23, R28, R29: 10000.0; R0603
R12, R13, R14, R15, R16, R17, R25: 100000.0; R0603
R24: 22.0; R0603
R26: 2231.0; R0603
R30: 9100.0; R0603
R31: 680000.0; R0603
R32: 120000.0; R0603
U1: stm32f205ZCT6; LQFP144
U2: M24M02-DRMN6TP; SOIC-8
U3: 0472192001; MOLEX_47219-2001
U4: MT28EW128ABA1HPC-0SIT; LBGA-64
U5: TMD27711; SMD-8
U6: ABS07-32.768KHZ-7-T
U7: ABLS-25.000MHZ-B2F-T
U8: LP3878SDX-ADJ/NOPB; WSON-8
U9: TPS3895ADRYR; SON-6
U10: 4-1437565-2; SW_4-1437565-2
U11: Q65110A2395; LGM67K-G1J2-24-Z
U12, U13: nc7sz125m5x; NC7SZ125M5X
U14: Dummy; DUMMY_PACKAGE_180

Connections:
CLK_CRYSTAL_U1_8: C19.1, U1.8, U6.1
CLK_CRYSTAL_U1_9: C20.1, U1.9, U6.2
CLK_CRYSTAL_U1_23: C21.1, U1.23, U7.1
CLK_CRYSTAL_U1_24: C22.1, U1.24, U7.2
GND: C1.2, C2.2, C3.2, C4.2, C5.2, C6.2, C7.2, C8.2, C9.2, C10.2, C11.2, C12.2, C13.2, C14.2, C15.2, C16.2, C17.2, C18.2, C19.2, C20.2, C21.2, C22.2, C23.2, C24.2, C25.2, C26.2, C27.2, C28.2, C29.2, C30.2, C31.2, C32.2, C33.2, C34.2, C35.2, C36.2, C37.2, J1.2, R2.2, R10.2, R11.2, R27.2, R30.2, R32.2, U1.16, U1.31, U1.38, U1.51, U1.61, U1.83, U1.94, U1.107, U1.120, U1.130, U2.4, U3.6, U3.G1, U3.G2, U3.G3, U3.G4, U4.E8, U4.H2, U4.H7, U5.3, U8.3, U8.PAD, U9.2, U11.C, U12.1, U12.3, U13.1, U13.3, U14.1
NET_U1_25: R5.1, U1.25, U13.4
NET_U1_33: C17.1, C18.1, F1.1, U1.32, U1.33
NET_U1_69: R8.1, U1.69, U2.6
NET_U1_70: R9.1, U1.70, U2.5
NET_U1_71: C15.1, U1.71
NET_U1_106: C16.1, U1.106
NET_U1_136: R6.1, U1.136, U5.2
NET_U1_137: R7.1, U1.137, U5.8
NET_U1_138: R10.1, U1.138
NET_U1_142: U10.3, U10.4
NET_U2_3: R11.1, U2.3
NET_U4_B4: R21.1, U4.B4
NET_U4_B5: R4.1, U4.B5, U12.4
NET_U5_4: C29.1, R24.1, U5.4
NET_U5_7: R23.1, U5.7
NET_U8_1: C30.1, U8.1
NET_U8_6: R26.2, R27.1, U8.6
NET_U8_8: R25.1, U8.8
NET_U9_1: R29.1, R30.1, U9.1
NET_U9_3: R31.2, R32.1, U9.3
NET_U9_4: R28.1, U9.4, U12.2, U13.2
NET_U10_1: R2.1, U10.1, U10.2
PROC_FSMC_A0: U1.10, U4.E2
PROC_FSMC_A1: U1.11, U4.D2
PROC_FSMC_A2: U1.12, U4.C2
PROC_FSMC_A3: U1.13, U4.A2
PROC_FSMC_A4: U1.14, U4.B2
PROC_FSMC_A5: U1.15, U4.D3
PROC_FSMC_A6: U1.50, U4.C3
PROC_FSMC_A7: U1.53, U4.A3
PROC_FSMC_A8: U1.54, U4.B6
PROC_FSMC_A9: U1.55, U4.A6
PROC_FSMC_A10: U1.56, U4.C6
PROC_FSMC_A11: U1.57, U4.D6
PROC_FSMC_A12: U1.87, U4.B7
PROC_FSMC_A13: U1.88, U4.A7
PROC_FSMC_A14: U1.89, U4.C7
PROC_FSMC_A15: U1.90, U4.D7
PROC_FSMC_A16: U1.80, U4.E7
PROC_FSMC_A17: U1.81, U4.B3
PROC_FSMC_A18: U1.82, U4.C4
PROC_FSMC_A19: U1.2, U4.D5
PROC_FSMC_A20: U1.3, U4.D4
PROC_FSMC_A21: U1.4, U4.C5
PROC_FSMC_A22: U1.5, U4.B8
PROC_FSMC_D0: U1.85, U4.E3
PROC_FSMC_D1: U1.86, U4.H3
PROC_FSMC_D2: U1.114, U4.E4
PROC_FSMC_D3: U1.115, U4.H4
PROC_FSMC_D4: U1.58, U4.H5
PROC_FSMC_D5: U1.59, U4.E5
PROC_FSMC_D6: U1.60, U4.H6
PROC_FSMC_D7: U1.63, U4.E6
PROC_FSMC_D8: U1.64, U4.F3
PROC_FSMC_D9: U1.65, U4.G3
PROC_FSMC_D10: U1.66, U4.F4
PROC_FSMC_D11: U1.67, U4.G4
PROC_FSMC_D12: U1.68, U4.F5
PROC_FSMC_D13: U1.77, U4.G6
PROC_FSMC_D14: U1.78, U4.F6
PROC_FSMC_D15: U1.79, U4.G7
PROC_FSMC_NBL0: R22.1, U1.141, U4.F7
PROC_FSMC_NE1: R18.1, U1.123, U4.F2
PROC_FSMC_NOE: R19.1, U1.118, U4.G2
PROC_FSMC_NWAIT: U1.122, U4.A4
PROC_FSMC_NWE: R20.1, U1.119, U4.A5
PROC_SDIO_CK: R13.1, U1.113, U3.5
PROC_SDIO_CMD: R12.1, U1.116, U3.3
PROC_SDIO_D0: R14.1, U1.98, U3.7
PROC_SDIO_D1: R15.1, U1.99, U3.8
PROC_SDIO_D2: R16.1, U1.111, U3.1
PROC_SDIO_D3: R17.1, U1.112, U3.2
PROC_TIM1_CH2N: U1.46, U14.2
PROC_TIM1_CH3N: U1.47, U14.3
VCC_S1_7V8: C31.1, C34.1, C35.1, J1.1, R25.2, U8.4
VCC_TIER1_3V3: C1.1, C2.1, C3.1, C4.1, C5.1, C6.1, C7.1, C8.1, C9.1, C10.1, C11.1, C12.1, C13.1, C14.1, C23.1, C24.1, C25.1, C26.1, C27.1, C28.1, C32.1, C33.1, C36.1, C37.1, F1.2, R4.2, R5.2, R6.2, R7.2, R8.2, R9.2, R12.2, R13.2, R14.2, R15.2, R16.2, R17.2, R18.2, R19.2, R20.2, R21.2, R22.2, R23.2, R24.2, R26.1, R28.2, R29.2, R31.1, U1.6, U1.17, U1.30, U1.39, U1.52, U1.62, U1.72, U1.84, U1.95, U1.108, U1.121, U1.131, U1.144, U2.8, U3.4, U4.D8, U4.F1, U4.G5, U5.1, U8.5, U9.6, U12.5, U13.5
